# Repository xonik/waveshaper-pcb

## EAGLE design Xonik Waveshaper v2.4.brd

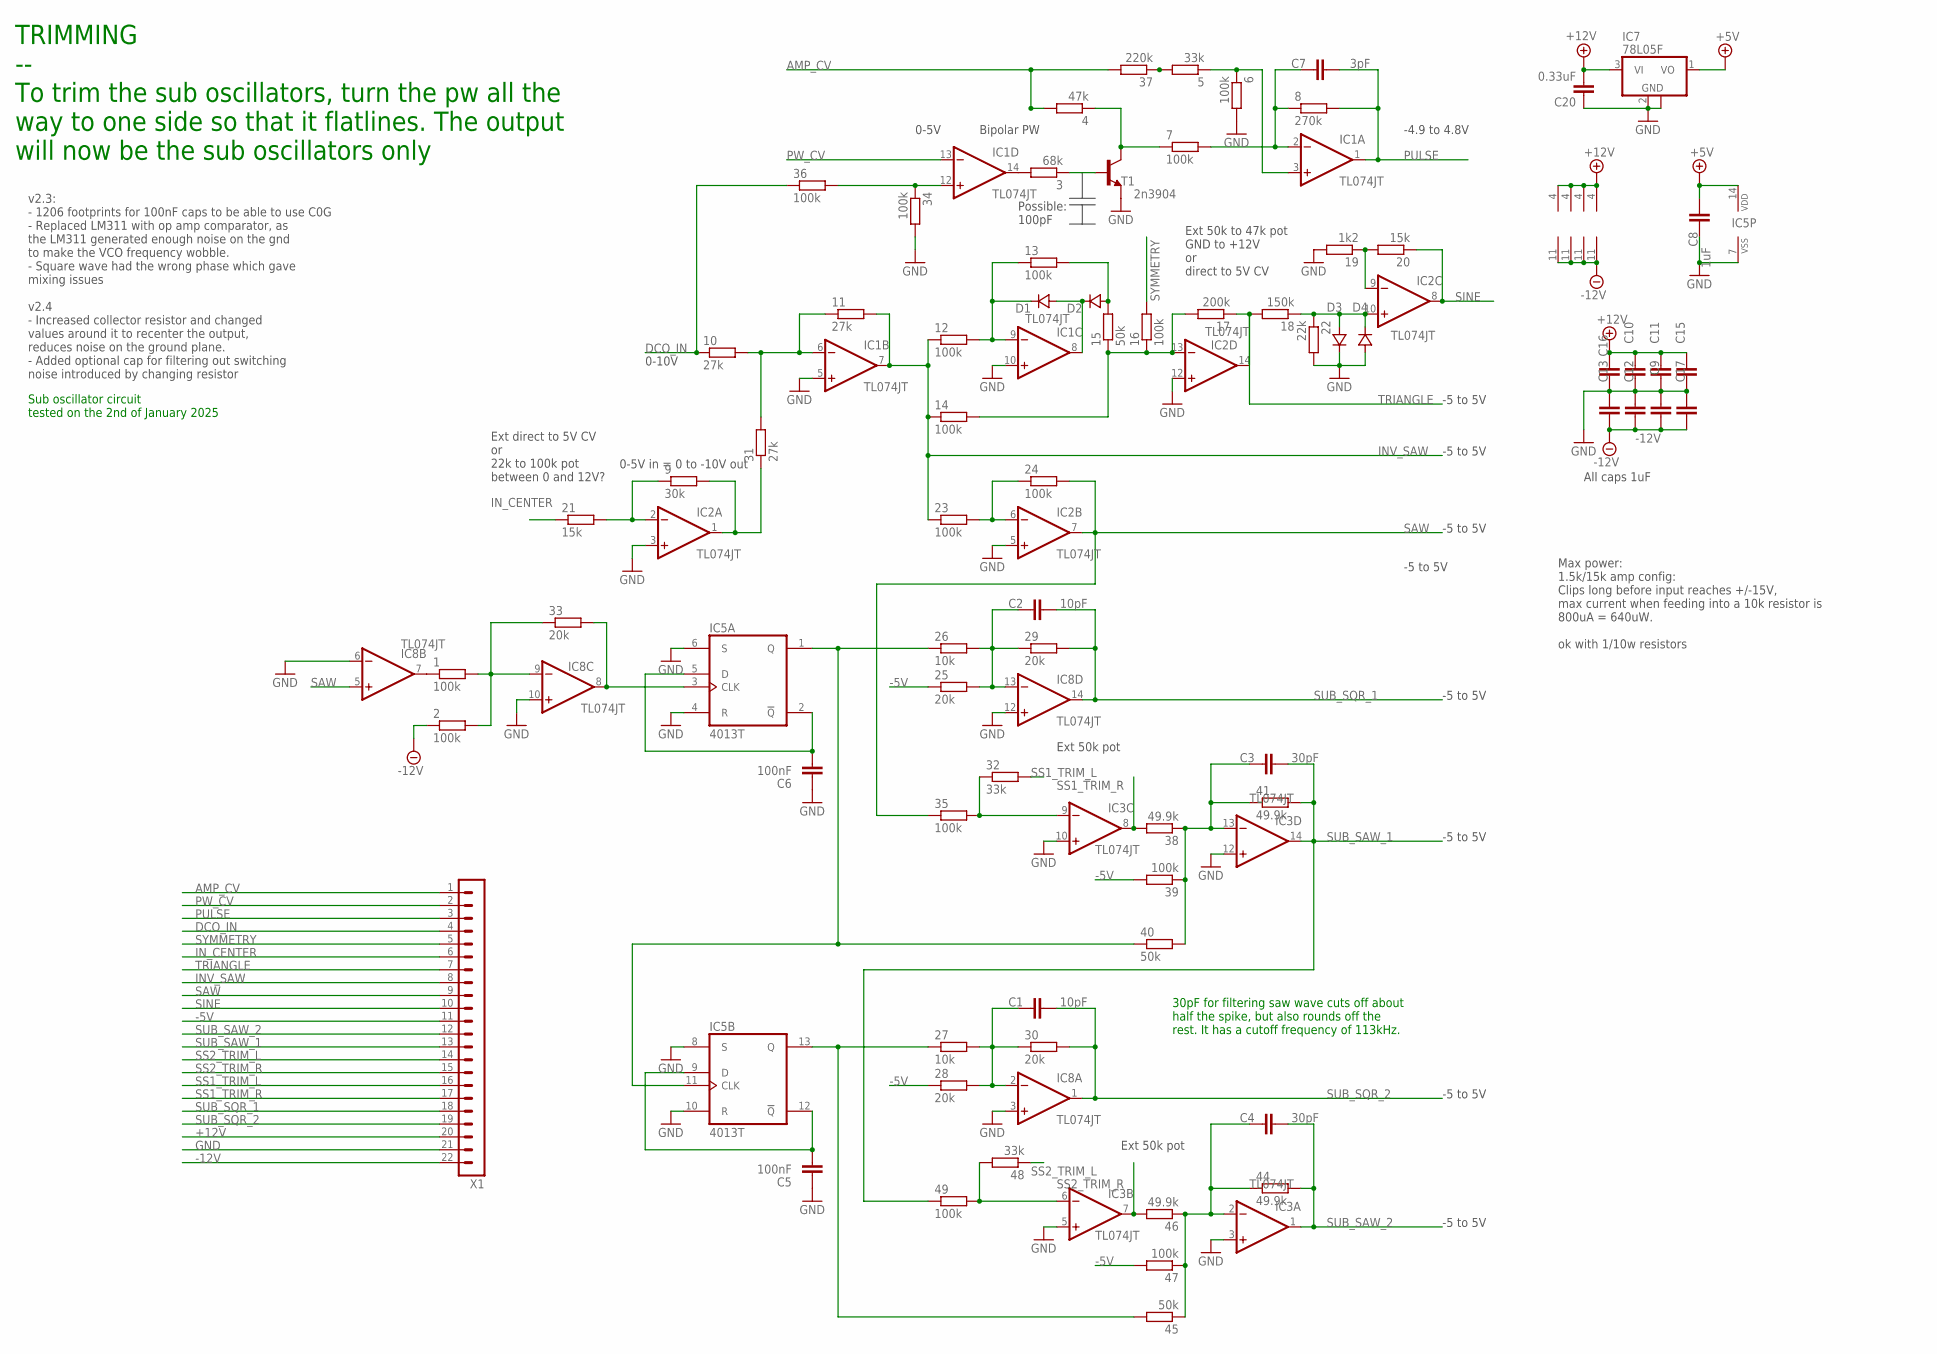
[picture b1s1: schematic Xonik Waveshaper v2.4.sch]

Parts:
1, 2, 6, 7, 12, 14, 16, 23, 35, 39, 47, 49: 100k; R0603
3: 68k; R0603
4: 47k; R0603
5, 32, 48: 33k; R0603
8: 270k; R0603
9: 30k; R0603
10, 11, 31: 27k; R0603
13, 24, 34, 36: 100k; R0402
15, 40, 45: 50k; R0603
17: 200k; R0603
18: 150k; R0603
19: 1k2; R0603
20, 21: 15k; R0603
22: 22k; R0603
25, 28, 29, 30, 33: 20k; R0603
26, 27: 10k; R0603
37: 220k; R0603
38, 41, 44, 46: 49.9k; R0603
C1, C2: 10pF; C0603-J
C3, C4: 30pF; C0603-J
C5, C6: 100nF; C1206
C7: 3pF; C0603-J
C8, C9, C10, C11, C12, C13, C15, C16, C17: 1uF; C0402-J
C20: 0.33uF; C0603-J
D1, D2, D3, D4: 1N41480805; D0805-J
IC1, IC2, IC3, IC8: TL074JT; TSSOP14J
IC5: 4013T; TSSOP14J
IC7: 78L05F; SOT89
T1: 2n3904; SOT23-BEC
X1: MA22-1JN; MA22N-1J

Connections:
+5V: C8.2, IC5.14 (VDD), IC7.1 (VO)
+12V: C10.2, C11.2, C15.2, C16.2, C20.2, IC1.4 (V+), IC2.4 (V+), IC3.4 (V+), IC7.3 (VI), IC8.4 (V+), X1.20
-5V: 25.1, 28.1, 39.2, 47.2, X1.11
-12V: 2.1, C9.1, C12.1, C13.1, C17.1, IC1.11 (V-), IC2.11 (V-), IC3.11 (V-), IC8.11 (V-), X1.22
AMP_CV: 4.2, 37.2, X1.1
DCO_IN: 10.1, 36.1, X1.4
GND: 6.2, 19.2, 22.2, 34.2, C5.1, C6.1, C8.1, C9.2, C10.1, C11.1, C12.2, C13.2, C15.1, C16.1, C17.2, C20.1, D3.C, D4.A, IC1.5 (+IN), IC1.10 (+IN), IC2.3 (+IN), IC2.5 (+IN), IC2.12 (+IN), IC3.3 (+IN), IC3.5 (+IN), IC3.10 (+IN), IC3.12 (+IN), IC5.4 (R), IC5.6 (S), IC5.7 (VSS), IC5.8 (S), IC5.10 (R), IC7.2 (GND), IC7.2@1 (GND), IC8.3 (+IN), IC8.6 (-IN), IC8.10 (+IN), IC8.12 (+IN), T1.E, X1.21
INV_SAW: 11.2, 12.1, 14.1, 23.1, IC1.7 (OUT), X1.8
IN_CENTER: 21.1, X1.6
unnamed: 9.1, 21.2, IC2.2 (-IN)
unnamed: 3.2, IC1.14 (OUT)
unnamed: 3.1, T1.B
unnamed: 4.1, 7.1, T1.C
unnamed: 5.1, 6.1, IC1.3 (+IN)
unnamed: 7.2, 8.1, C7.1, IC1.2 (-IN)
unnamed: 1.1, IC8.7 (OUT)
unnamed: 34.1, 36.2, IC1.12 (+IN)
unnamed: 1.2, 2.2, 33.1, IC8.9 (-IN)
unnamed: 10.2, 11.1, 31.2, IC1.6 (-IN)
unnamed: 12.2, 13.1, D1.C, IC1.9 (-IN)
unnamed: D1.A, D2.C, IC1.8 (OUT)
unnamed: 13.2, 15.2, D2.A
unnamed: 14.2, 15.1, 16.1, 17.2, IC2.13 (-IN)
unnamed: 23.2, 24.1, IC2.6 (-IN)
unnamed: 5.2, 37.1
unnamed: 33.2, IC5.3 (CLK), IC8.8 (OUT)
unnamed: 25.2, 26.2, 29.1, C2.1, IC8.13 (-IN)
unnamed: 48.2, 49.2, IC3.6 (-IN)
unnamed: 27.2, 28.2, 30.1, C1.1, IC8.2 (-IN)
unnamed: 32.1, 35.2, IC3.9 (-IN)
unnamed: 38.1, 39.1, 40.2, 41.1, C3.1, IC3.13 (-IN)
unnamed: 44.1, 45.1, 46.1, 47.1, C4.1, IC3.2 (-IN)
unnamed: C6.2, IC5.2 (!Q), IC5.5 (D)
unnamed: 26.1, 40.1, IC5.1 (Q), IC5.11 (CLK)
unnamed: C5.2, IC5.9 (D), IC5.12 (!Q)
unnamed: 27.1, 45.2, IC5.13 (Q)
unnamed: 19.1, 20.2, IC2.9 (-IN)
unnamed: 18.1, 22.1, D3.A, D4.C, IC2.10 (+IN)
unnamed: 9.2, 31.1, IC2.1 (OUT)
PULSE: 8.2, C7.2, IC1.1 (OUT), X1.3
PW_CV: IC1.13 (-IN), X1.2
SAW: 24.2, 35.1, IC2.7 (OUT), IC8.5 (+IN), X1.9
SINE: 20.1, IC2.8 (OUT), X1.10
SS1_TRIM_L: 32.2, X1.16
SS1_TRIM_R: 38.2, IC3.8 (OUT), X1.17
SS2_TRIM_L: 48.1, X1.14
SS2_TRIM_R: 46.2, IC3.7 (OUT), X1.15
SUB_SAW_1: 41.2, 49.1, C3.2, IC3.14 (OUT), X1.13
SUB_SAW_2: 44.2, C4.2, IC3.1 (OUT), X1.12
SUB_SQR_1: 29.2, C2.2, IC8.14 (OUT), X1.18
SUB_SQR_2: 30.2, C1.2, IC8.1 (OUT), X1.19
SYMMETRY: 16.2, X1.5
TRIANGLE: 17.1, 18.2, IC2.14 (OUT), X1.7

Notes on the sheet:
All caps 1uF
Ext direct to 5V CV or 22k to 100k pot between 0 and 12V?
Ext 50k to 47k pot GND to +12V or direct to 5V CV
Ext 50k pot
30pF for filtering saw wave cuts off about half the spike, but also rounds off the rest. It has a cutoff frequency of 113kHz.
Max power: 1.5k/15k amp config: Clips long before input reaches +/-15V, max current when feeding into a 10k resistor is 800uA = 640uW. ok with 1/10w resistors
0-5V in = 0 to -10V out
0-10V
0-5V
-4.9 to 4.8V
Bipolar PW
-5 to 5V
TRIMMING -- To trim the sub oscillators, turn the pw all the way to one side so that it flatlines. The output will now be the sub oscillators only
v2.3: - 1206 footprints for 100nF caps to be able to use C0G - Replaced LM311 with op amp comparator, as the LM311 generated enough noise on the gnd to make the VCO frequency wobble. - Square wave had the wrong phase which gave mixing issues v2.4 - Increased collector resistor and changed values ar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
Sub oscillator circuit tested on the 2nd of January 2025
Possible: 100pF

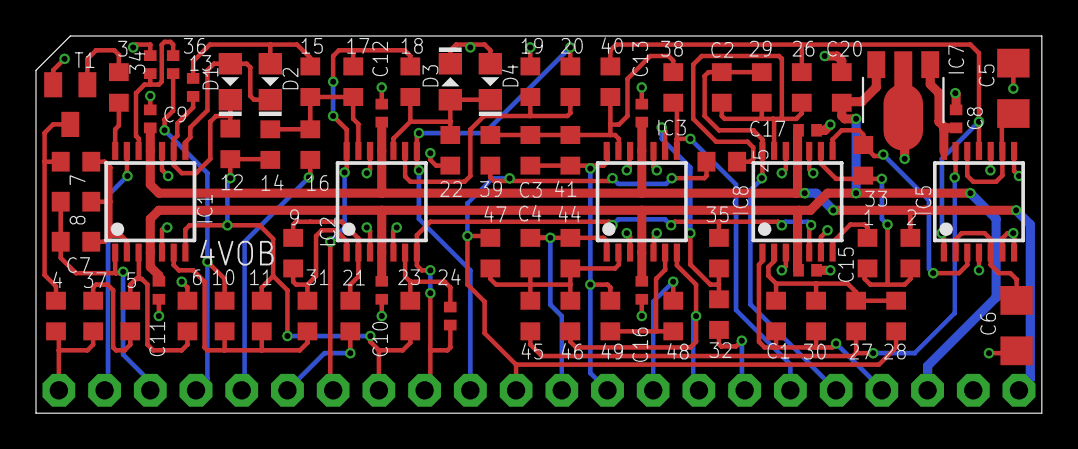
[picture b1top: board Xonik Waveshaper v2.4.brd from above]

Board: 4 copper layers, 55.9 x 21.0 mm, 77 parts (1 on the bottom side), 53 nets.

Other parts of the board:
U$1: XONIK_LOGO_40

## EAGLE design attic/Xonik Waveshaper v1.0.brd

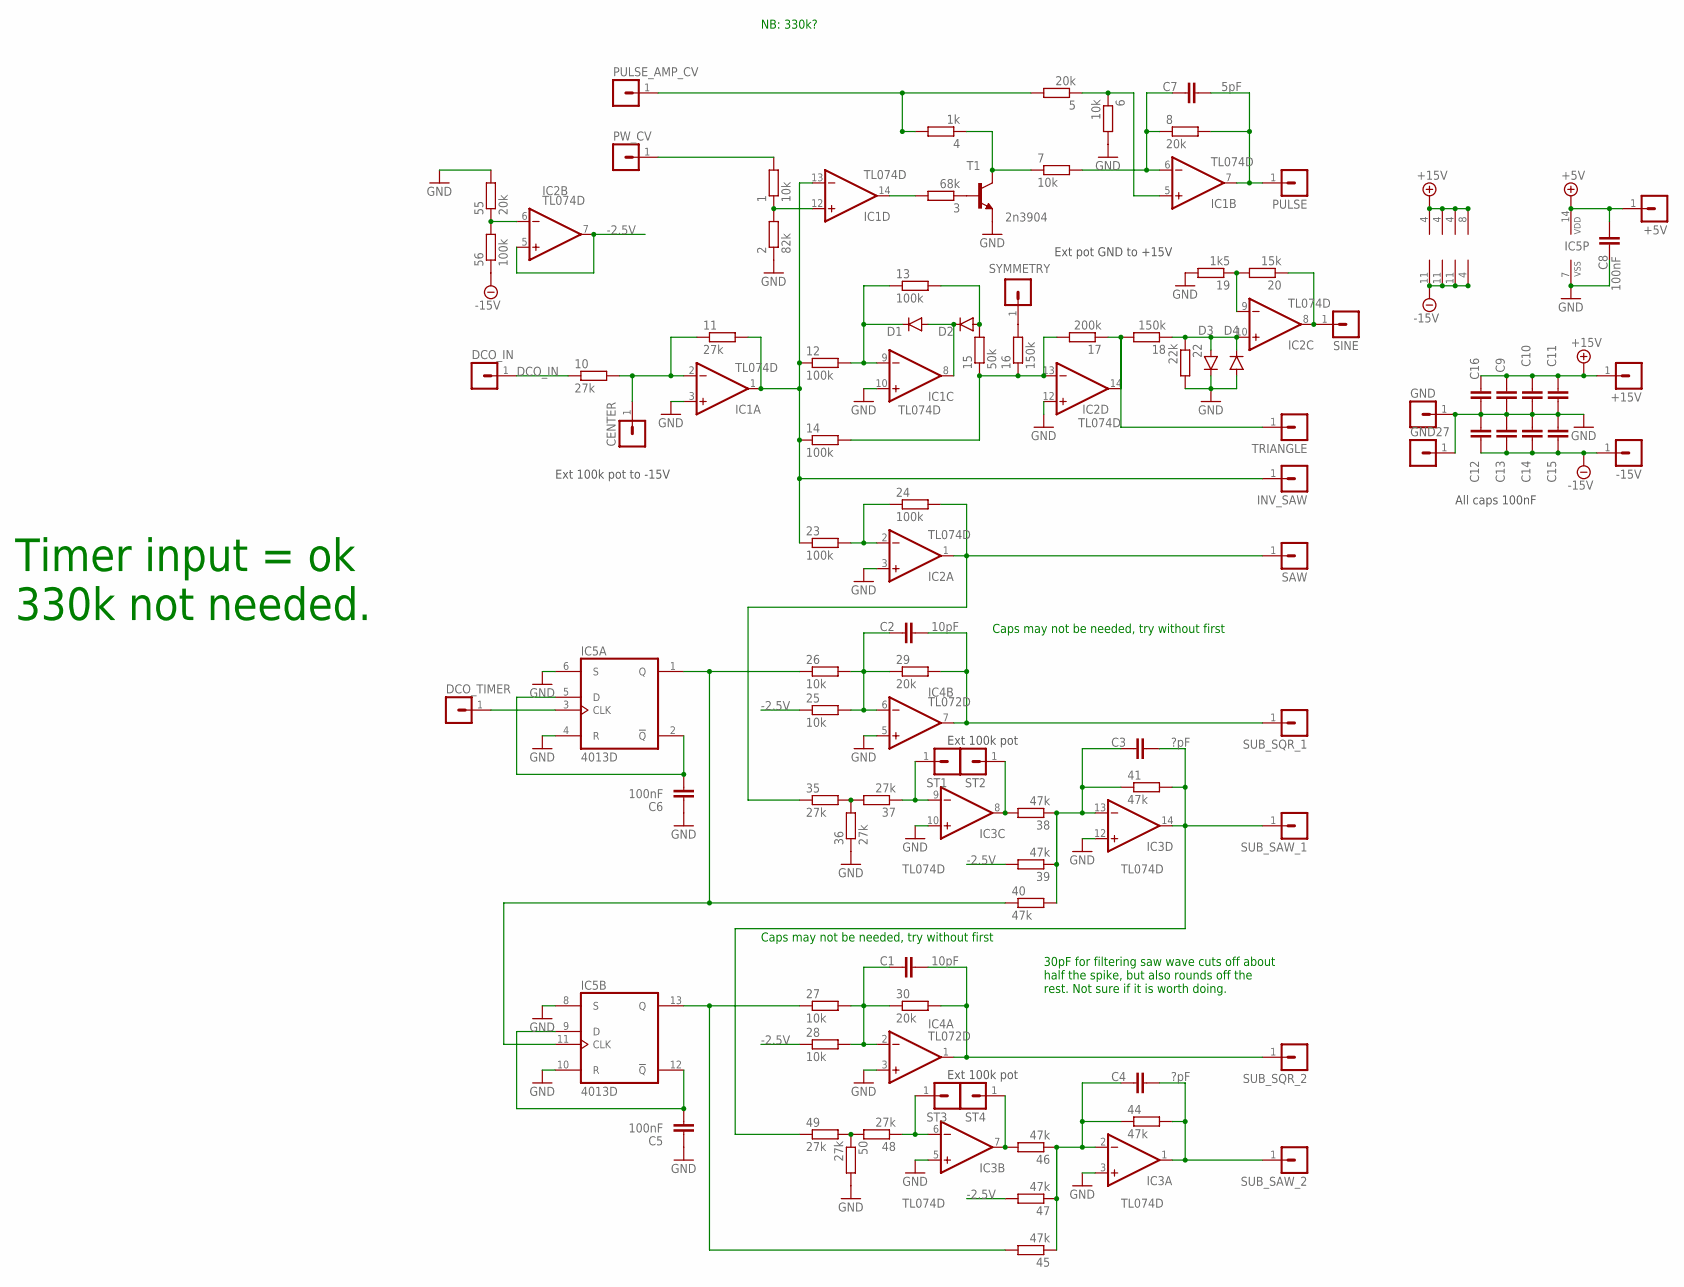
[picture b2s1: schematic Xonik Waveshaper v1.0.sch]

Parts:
1, 6, 7, 25, 26, 27, 28: 10k; R0805
2: 82k; R0805
3: 68k; R0805
4: 1k; R0805
5, 8, 29, 30, 55: 20k; R0805
10, 11, 35, 36, 37, 48, 49, 50: 27k; R0805
12, 13, 14, 23, 24, 56: 100k; R0805
15: 50k; R0805
16, 18: 150k; R0805
17: 200k; R0805
19: 1k5; R0805
20: 15k; R0805
22: 22k; R0805
38, 39, 40, 41, 44, 45, 46, 47: 47k; R0805
+5V, +15V: MA01-1JP; SIP-PIN01-1J
-15V: MA01-1JP; SIP-PIN01-1J
C1, C2: 10pF; C0805
C3, C4: ?pF; C0805
C5, C6, C8: 100nF; C0805
C7: 5pF; C0805
C9, C10, C11, C12, C13, C14, C15, C16: 100nF; C0603K
CENTER: MA01-1JP; SIP-PIN01-1J
D1, D2, D3, D4: 1N41480805; D0805-J
DCO_IN: MA01-1JP; SIP-PIN01-1J
DCO_TIMER: MA01-1JP; SIP-PIN01-1J
GND, GND27: MA01-1JP; SIP-PIN01-1J
IC1, IC2, IC3: TL074D; SO14
IC4: TL072D; SO08J
IC5: 4013D; SO14J
INV_SAW: MA01-1JP; SIP-PIN01-1J
PULSE: MA01-1JP; SIP-PIN01-1J
PULSE_AMP_CV: MA01-1JP; SIP-PIN01-1J
PW_CV: MA01-1JP; SIP-PIN01-1J
SAW: MA01-1JP; SIP-PIN01-1J
SINE: MA01-1JP; SIP-PIN01-1J
ST1, ST2, ST3, ST4: MA01-1JP; SIP-PIN01-1J
SUB_SAW_1, SUB_SAW_2: MA01-1JP; SIP-PIN01-1J
SUB_SQR_1, SUB_SQR_2: MA01-1JP; SIP-PIN01-1J
SYMMETRY: MA01-1JP; SIP-PIN01-1J
T1: 2n3904; SOT23-BEC
TRIANGLE: MA01-1JP; SIP-PIN01-1J

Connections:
+5V: +5V.1, C8.2, IC5.14 (VDD)
+15V: +15V.1, C9.2, C10.2, C11.2, C16.2, IC1.4 (V+), IC2.4 (V+), IC3.4 (V+), IC4.8 (V+)
-2.5V: 25.1, 28.1, 39.2, 47.2, IC2.5 (+IN), IC2.7 (OUT)
-15V: 56.1, -15V.1, C12.1, C13.1, C14.1, C15.1, IC1.11 (V-), IC2.11 (V-), IC3.11 (V-), IC4.4 (V-)
AMP_CV: 4.2, 5.2, PULSE_AMP_CV.1
DCO_IN: 10.1, DCO_IN.1
GND: 2.1, 6.2, 19.2, 22.2, 36.1, 50.2, 55.2, C5.1, C6.1, C8.1, C9.1, C10.1, C11.1, C12.2, C13.2, C14.2, C15.2, C16.1, D3.C, D4.A, GND.1, GND27.1, IC1.3 (+IN), IC1.10 (+IN), IC2.3 (+IN), IC2.12 (+IN), IC3.3 (+IN), IC3.5 (+IN), IC3.10 (+IN), IC3.12 (+IN), IC4.3 (+IN), IC4.5 (+IN), IC5.4 (R), IC5.6 (S), IC5.7 (VSS), IC5.8 (S), IC5.10 (R), T1.E
unnamed: 1.1, 2.2, IC1.12 (+IN)
unnamed: 3.2, IC1.14 (OUT)
unnamed: 3.1, T1.B
unnamed: 4.1, 7.1, T1.C
unnamed: 5.1, 6.1, IC1.5 (+IN)
unnamed: 7.2, 8.1, C7.1, IC1.6 (-IN)
unnamed: 8.2, C7.2, IC1.7 (OUT), PULSE.1
unnamed: 11.2, 12.1, 14.1, 23.1, IC1.1 (OUT), IC1.13 (-IN), INV_SAW.1
unnamed: 10.2, 11.1, CENTER.1, IC1.2 (-IN)
unnamed: 12.2, 13.1, D1.C, IC1.9 (-IN)
unnamed: D1.A, D2.C, IC1.8 (OUT)
unnamed: 13.2, 15.2, D2.A
unnamed: 14.2, 15.1, 16.1, 17.2, IC2.13 (-IN)
unnamed: 23.2, 24.1, IC2.2 (-IN)
unnamed: 24.2, 35.1, IC2.1 (OUT), SAW.1
unnamed: 29.2, C2.2, IC4.7 (OUT), SUB_SQR_1.1
unnamed: 30.2, C1.2, IC4.1 (OUT), SUB_SQR_2.1
unnamed: 25.2, 26.2, 29.1, C2.1, IC4.6 (-IN)
unnamed: 46.2, IC3.7 (OUT), ST4.1
unnamed: 48.2, 49.2, 50.1
unnamed: 27.2, 28.2, 30.1, C1.1, IC4.2 (-IN)
unnamed: 35.2, 36.2, 37.2
unnamed: 37.1, IC3.9 (-IN), ST1.1
unnamed: 38.1, 39.1, 40.2, 41.1, C3.1, IC3.13 (-IN)
unnamed: 41.2, 49.1, C3.2, IC3.14 (OUT), SUB_SAW_1.1
unnamed: 48.1, IC3.6 (-IN), ST3.1
unnamed: 44.1, 45.1, 46.1, 47.1, C4.1, IC3.2 (-IN)
unnamed: 44.2, C4.2, IC3.1 (OUT), SUB_SAW_2.1
unnamed: C6.2, IC5.2 (!Q), IC5.5 (D)
unnamed: 26.1, 40.1, IC5.1 (Q), IC5.11 (CLK)
unnamed: 55.1, 56.2, IC2.6 (-IN)
unnamed: C5.2, IC5.9 (D), IC5.12 (!Q)
unnamed: 27.1, 45.2, IC5.13 (Q)
unnamed: 19.1, 20.2, IC2.9 (-IN)
unnamed: 16.2, SYMMETRY.1
unnamed: 17.1, 18.2, IC2.14 (OUT), TRIANGLE.1
unnamed: 18.1, 22.1, D3.A, D4.C, IC2.10 (+IN)
unnamed: 20.1, IC2.8 (OUT), SINE.1
unnamed: 38.2, IC3.8 (OUT), ST2.1
PW_CV: 1.2, PW_CV.1
SQR: DCO_TIMER.1, IC5.3 (CLK)

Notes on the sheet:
NB: 330k?
All caps 100nF
Ext 100k pot to -15V
Ext pot GND to +15V
Ext 100k pot
Timer input = ok 330k not needed.
30pF for filtering saw wave cuts off about half the spike, but also rounds off the rest. Not sure if it is worth doing.
Caps may not be needed, try without first

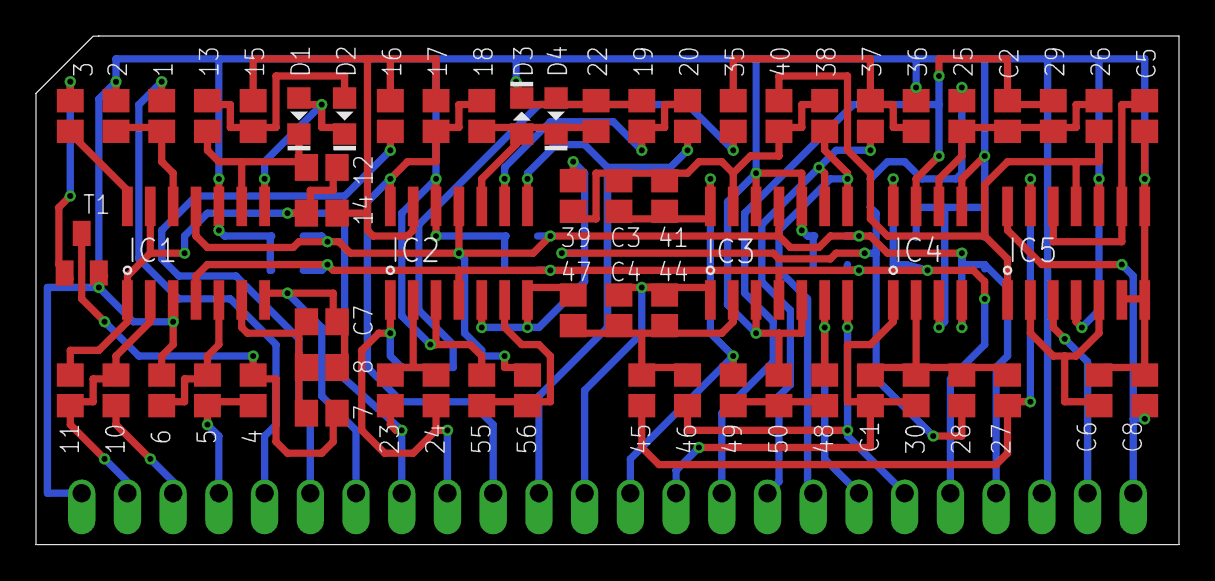
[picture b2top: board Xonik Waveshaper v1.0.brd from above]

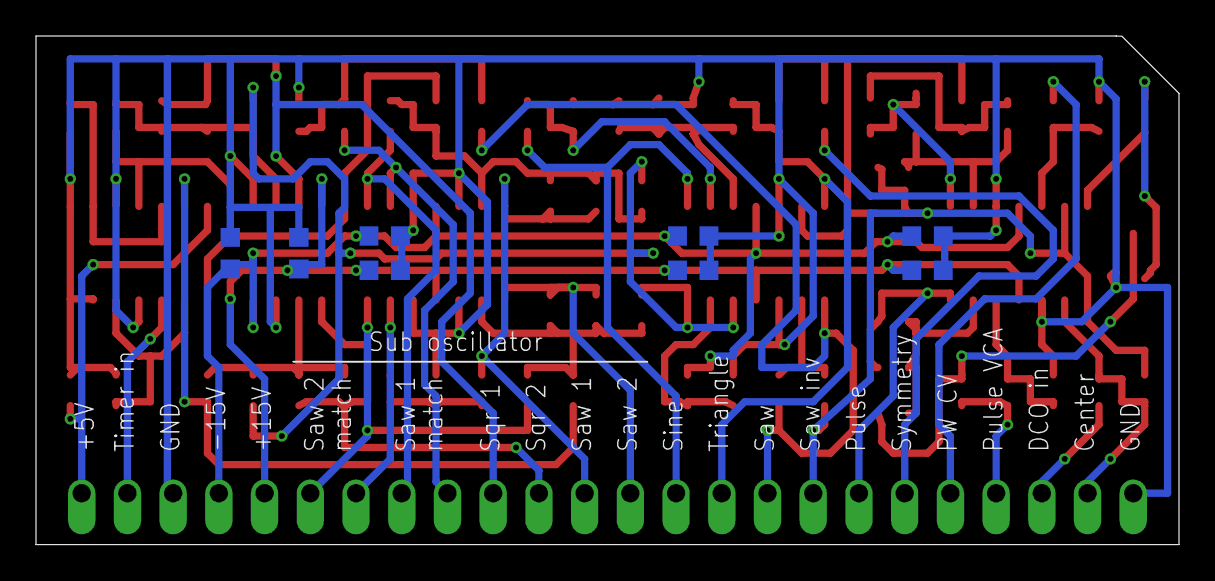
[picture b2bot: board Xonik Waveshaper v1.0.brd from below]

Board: 2 copper layers, 63.5 x 28.3 mm, 94 parts (8 on the bottom side), 48 nets.

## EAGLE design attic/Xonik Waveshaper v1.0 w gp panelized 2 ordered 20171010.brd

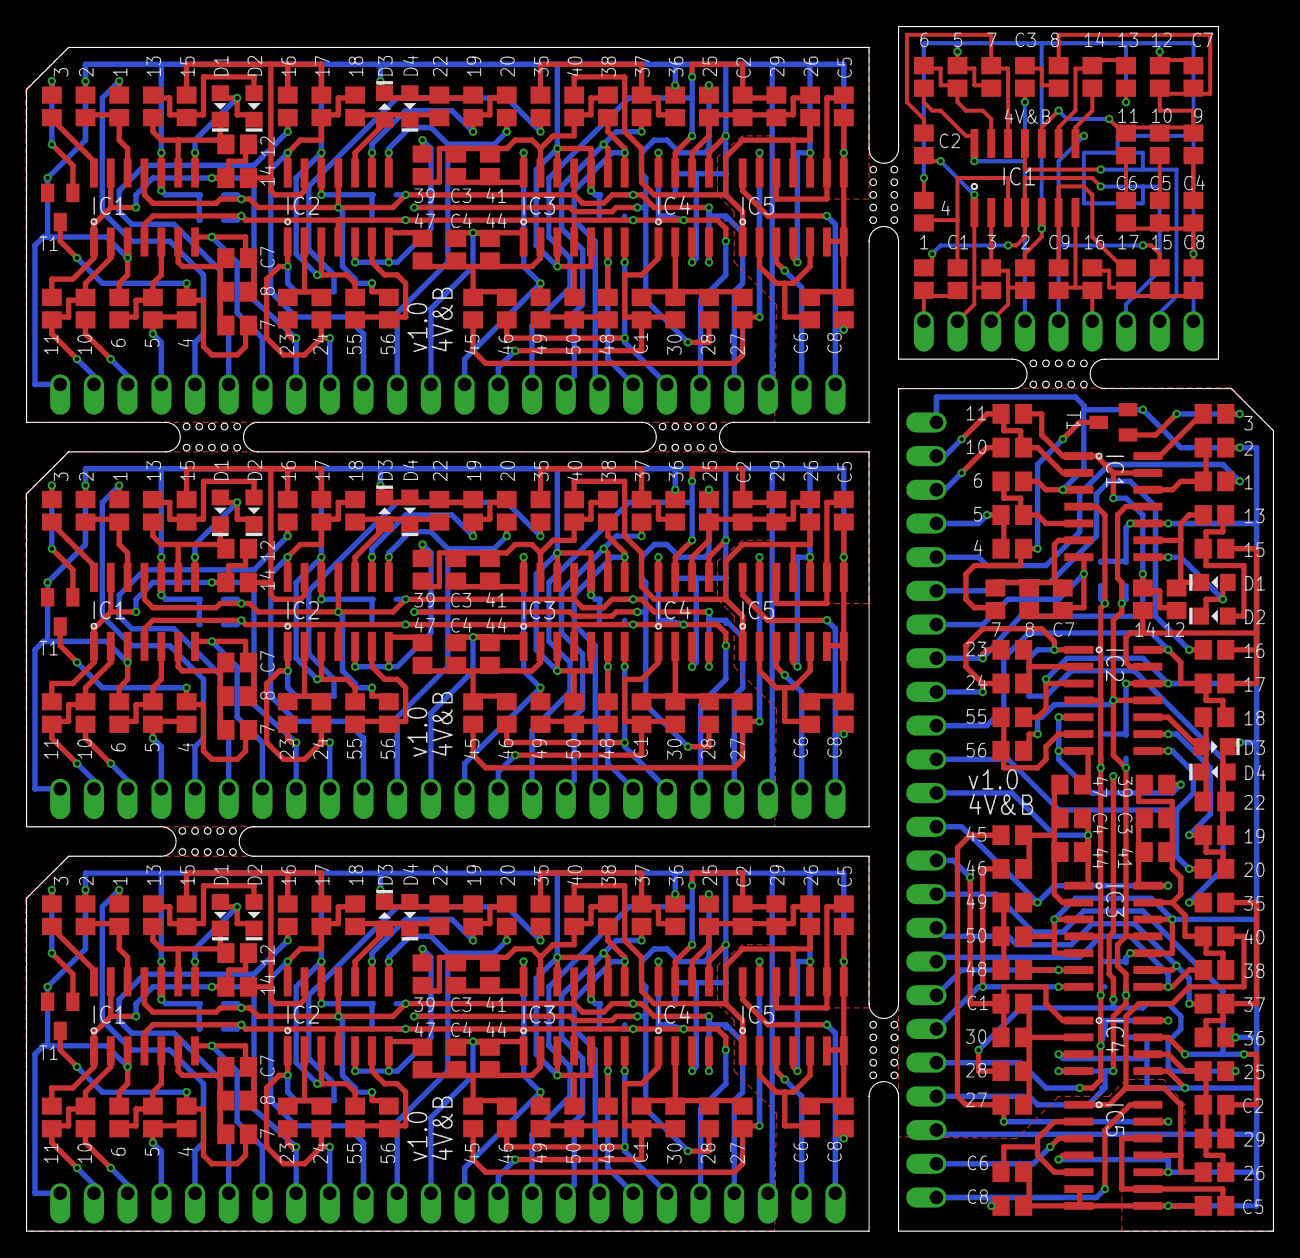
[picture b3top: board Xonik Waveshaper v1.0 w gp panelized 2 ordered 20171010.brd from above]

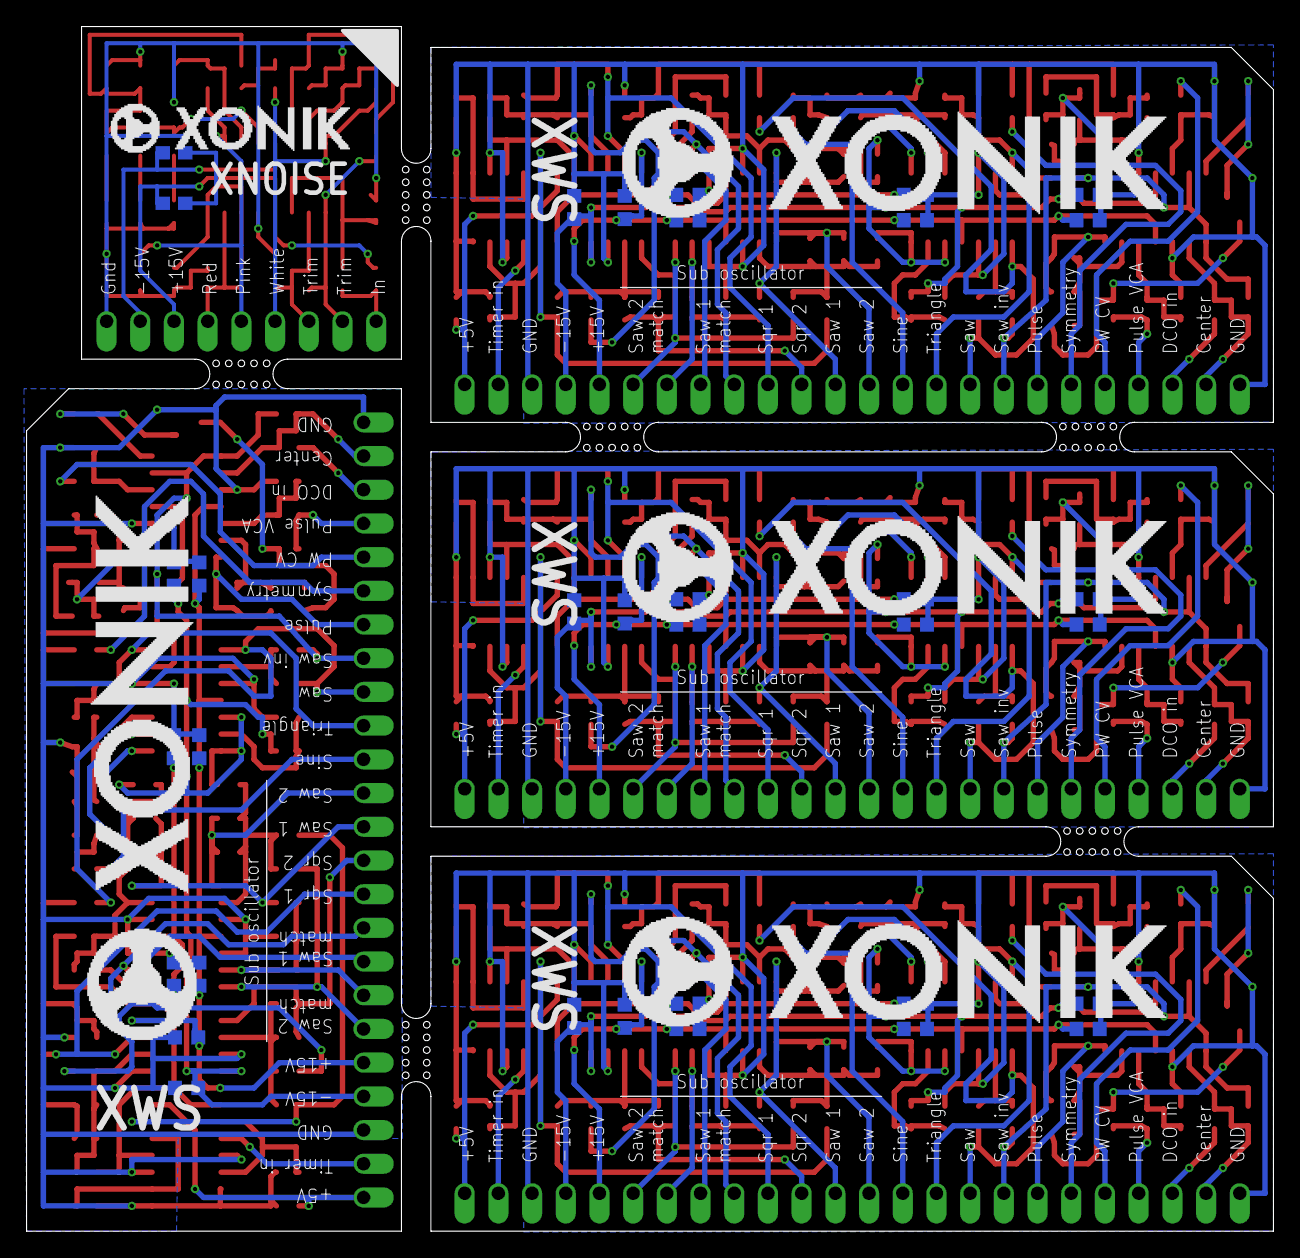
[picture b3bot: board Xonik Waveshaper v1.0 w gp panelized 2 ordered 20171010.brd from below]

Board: 2 copper layers, 94.0 x 90.8 mm, 414 parts (34 on the bottom side), 212 nets.

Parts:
1, 6, 7, 9, 25, 26, 27, 28, 34, 42, 67, 68, 69, 70, 89, 94, 95, 111, 112, 113, 114, 133, 138, 139, 155, 156, 157, 158, 186: 10k; R0805
2, 21, 90, 134: 82k; R0805
3, 31, 91, 135, 184: 68k; R0805
4, 32, 92, 136, 178, 181, 189: 1k; R0805
5, 8, 29, 30, 33, 43, 55, 71, 72, 87, 93, 96, 115, 116, 131, 137, 140, 159, 160, 175, 179, 182, 190: 20k; R0805
10, 11, 35, 36, 37, 48, 49, 50, 51, 52, 73, 74, 75, 84, 85, 86, 97, 98, 117, 118, 119, 128, 129, 130, 141, 142, 161, 162, 163, 172, 173, 174: 27k; R0805
12, 13, 14, 23, 24, 53, 54, 56, 57, 65, 66, 88, 99, 100, 101, 109, 110, 132, 143, 144, 145, 153, 154, 176, 180, 183: 100k; R0805
15, 58, 102, 146: 50k; R0805
16, 18, 59, 61, 103, 105, 147, 149: 150k; R0805
17, 60, 104, 148: 200k; R0805
19, 62, 106, 150: 1k5; R0805
20, 63, 107, 151, 192: 15k; R0805
22, 64, 108, 152: 22k; R0805
38, 39, 40, 41, 44, 45, 46, 47, 76, 77, 78, 79, 80, 81, 82, 83, 120, 121, 122, 123, 124, 125, 126, 127, 164, 165, 166, 167, 168, 169, 170, 171: 47k; R0805
177: 220k; R0805
185: 33.2k; R0805
187: 3k; R0805
188: 1M; R0805
191: 4k7; R0805
193: 301k; R0805
+5V, +5V1, +5V2, +5V3, +15V, +15V1, +15V2, +15V3, +15V4: SIP-PIN01-1J
-15V, -15V1, -15V2, -15V3, -15V4: SIP-PIN01-1J
C1, C2, C17, C18, C33, C34, C49, C50: 10pF; C0805
C3, C4, C19, C20, C35, C36, C51, C52: ?pF; C0805
C5, C6, C8, C21, C22, C32, C37, C38, C48, C53, C54, C64: 100nF; C0805
C7, C23, C39, C55: 5pF; C0805
C9, C10, C11, C12, C13, C14, C15, C16, C24, C25, C26, C27, C28, C29, C30, C31, C40, C41, C42, C43, C44, C45, C46, C47, C56, C57, C58, C59, C60, C61, C62, C63: 100nF; C0603K
C65, C66, C67: 470n; C0805
C68: 100n; C0805
C69: 22n; C0805
C70: 10n; C0805
C71: 3n3; C0805
C72: 220n; C0805
C73: 2n2; C0805
C74, C75: C0603
CENTER, CENTER1, CENTER2, CENTER3: SIP-PIN01-1J
D1, D2, D3, D4, D5, D6, D7, D8, D9, D10, D11, D12, D13, D14, D15, D16: 1N41480805; D0805-J
DCO_IN, DCO_IN1, DCO_IN2, DCO_IN3: SIP-PIN01-1J
DCO_TIMER, DCO_TIMER1, DCO_TIMER2, DCO_TIMER3: SIP-PIN01-1J
GND, GND1, GND2, GND3, GND4, GND5, GND6, GND7, GND27: SIP-PIN01-1J
IC1, IC2, IC3, IC6, IC7, IC8, IC11, IC12, IC13, IC16, IC17, IC18, IC21: TL074D; SO14
IC4, IC10, IC15, IC20: TL072D; SO08J
IC5, IC9, IC14, IC19: 4013D; SO14J
INV_SAW, INV_SAW1, INV_SAW2, INV_SAW3: SIP-PIN01-1J
LEVEL1, LEVEL2: SIP-PIN01-1J
NOISE_IN: SIP-PIN01-1J
PINK_OUT: SIP-PIN01-1J
PULSE, PULSE1, PULSE2, PULSE3: SIP-PIN01-1J
PULSE_AMP_CV, PULSE_AMP_CV1, PULSE_AMP_CV2, PULSE_AMP_CV3: SIP-PIN01-1J
PW_CV, PW_CV1, PW_CV2, PW_CV3: SIP-PIN01-1J
RED_OUT: SIP-PIN01-1J
SAW, SAW1, SAW2, SAW3: SIP-PIN01-1J
SINE, SINE1, SINE2, SINE3: SIP-PIN01-1J
ST1, ST2, ST3, ST4, ST5, ST6, ST7, ST8, ST9, ST10, ST11, ST12, ST13, ST14, ST15, ST16: SIP-PIN01-1J
SUB_SAW_1, SUB_SAW_2, SUB_SAW_3, SUB_SAW_4, SUB_SAW_5, SUB_SAW_6, SUB_SAW_7, SUB_SAW_8: SIP-PIN01-1J
SUB_SQR_1, SUB_SQR_2, SUB_SQR_3, SUB_SQR_4, SUB_SQR_5, SUB_SQR_6, SUB_SQR_7, SUB_SQR_8: SIP-PIN01-1J
SYMMETRY, SYMMETRY1, SYMMETRY2, SYMMETRY3: SIP-PIN01-1J
T1, T2, T3, T4: 2n3904; SOT23-BEC
TRIANGLE, TRIANGLE1, TRIANGLE2, TRIANGLE3: SIP-PIN01-1J
WHITE_OUT: SIP-PIN01-1J

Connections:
+5V: +5V.1, C8.2, IC5.14
+5V1: +5V1.1, C32.2, IC9.14
+5V2: +5V2.1, C48.2, IC14.14
+5V3: +5V3.1, C64.2, IC19.14
+15V: +15V.1, C9.2, C10.2, C11.2, C16.2, IC1.4, IC2.4, IC3.4, IC4.8
+15V1: +15V1.1, C24.2, C25.2, C26.2, C27.2, IC6.4, IC7.4, IC8.4, IC10.8
+15V2: +15V2.1, C40.2, C41.2, C42.2, C43.2, IC11.4, IC12.4, IC13.4, IC15.8
+15V3: +15V3.1, C56.2, C57.2, C58.2, C59.2, IC16.4, IC17.4, IC18.4, IC20.8
+15V4: 177.2, +15V4.1, C74.2, IC21.4
-2.5V: 25.1, 28.1, 39.2, 47.2, IC2.5, IC2.7
-2.5V1: 67.1, 70.1, 77.2, 83.2, IC7.5, IC7.7
-2.5V2: 111.1, 114.1, 121.2, 127.2, IC12.5, IC12.7
-2.5V3: 155.1, 158.1, 165.2, 171.2, IC17.5, IC17.7
-15V: 56.1, -15V.1, C12.1, C13.1, C14.1, C15.1, IC1.11, IC2.11, IC3.11, IC4.4
-15V1: 88.1, -15V1.1, C28.1, C29.1, C30.1, C31.1, IC6.11, IC7.11, IC8.11, IC10.4
-15V2: 132.1, -15V2.1, C44.1, C45.1, C46.1, C47.1, IC11.11, IC12.11, IC13.11, IC15.4
-15V3: 176.1, -15V3.1, C60.1, C61.1, C62.1, C63.1, IC16.11, IC17.11, IC18.11, IC20.4
-15V4: -15V4.1, C75.1, IC21.11
AMP_CV: 4.2, 5.2, PULSE_AMP_CV.1
AMP_CV1: 32.2, 33.2, PULSE_AMP_CV1.1
AMP_CV2: 92.2, 93.2, PULSE_AMP_CV2.1
AMP_CV3: 136.2, 137.2, PULSE_AMP_CV3.1
DCO_IN: 10.1, DCO_IN.1
DCO_IN1: 51.1, DCO_IN1.1
DCO_IN2: 97.1, DCO_IN2.1
DCO_IN3: 141.1, DCO_IN3.1
GND: 2.1, 6.2, 19.2, 22.2, 36.1, 50.2, 55.2, C5.1, C6.1, C8.1, C9.1, C10.1, C11.1, C12.2, C13.2, C14.2, C15.2, C16.1, D3.C, D4.A, GND.1, GND27.1, IC1.3, IC1.10, IC2.3, IC2.12, IC3.3, IC3.5, IC3.10, IC3.12, IC4.3, IC4.5, IC5.4, IC5.6, IC5.7, IC5.8, IC5.10, T1.E
GND1: 21.1, 34.2, 62.2, 64.2, 74.1, 86.2, 87.2, C21.1, C22.1, C24.1, C25.1, C26.1, C27.1, C28.2, C29.2, C30.2, C31.2, C32.1, D7.C, D8.A, GND1.1, GND2.1, IC6.3, IC6.10, IC7.3, IC7.12, IC8.3, IC8.5, IC8.10, IC8.12, IC9.4, IC9.6, IC9.7, IC9.8, IC9.10, IC10.3, IC10.5, T2.E
GND2: 90.1, 94.2, 106.2, 108.2, 118.1, 130.2, 131.2, C37.1, C38.1, C40.1, C41.1, C42.1, C43.1, C44.2, C45.2, C46.2, C47.2, C48.1, D11.C, D12.A, GND3.1, GND4.1, IC11.3, IC11.10, IC12.3, IC12.12, IC13.3, IC13.5, IC13.10, IC13.12, IC14.4, IC14.6, IC14.7, IC14.8, IC14.10, IC15.3, IC15.5, T3.E
GND3: 134.1, 138.2, 150.2, 152.2, 162.1, 174.2, 175.2, C53.1, C54.1, C56.1, C57.1, C58.1, C59.1, C60.2, C61.2, C62.2, C63.2, C64.1, D15.C, D16.A, GND5.1, GND6.1, IC16.3, IC16.10, IC17.3, IC17.12, IC18.3, IC18.5, IC18.10, IC18.12, IC19.4, IC19.6, IC19.7, IC19.8, IC19.10, IC20.3, IC20.5, T4.E
GND4: 178.2, 180.2, 181.1, 183.1, 188.2, 189.1, C68.1, C69.1, C70.1, C71.1, C72.1, C74.1, C75.2, GND7.1, IC21.5
unnamed: 1.1, 2.2, IC1.12
unnamed: 3.2, IC1.14
unnamed: 3.1, T1.B
unnamed: 4.1, 7.1, T1.C
unnamed: 5.1, 6.1, IC1.5
unnamed: 7.2, 8.1, C7.1, IC1.6
unnamed: 8.2, C7.2, IC1.7, PULSE.1
unnamed: 9.1, 21.2, IC6.12
unnamed: 11.2, 12.1, 14.1, 23.1, IC1.1, IC1.13, INV_SAW.1
unnamed: 10.2, 11.1, CENTER.1, IC1.2
unnamed: 12.2, 13.1, D1.C, IC1.9
unnamed: D1.A, D2.C, IC1.8
unnamed: 13.2, 15.2, D2.A
unnamed: 14.2, 15.1, 16.1, 17.2, IC2.13
unnamed: 23.2, 24.1, IC2.2
unnamed: 24.2, 35.1, IC2.1, SAW.1
unnamed: 29.2, C2.2, IC4.7, SUB_SQR_1.1
unnamed: 30.2, C1.2, IC4.1, SUB_SQR_2.1
unnamed: 25.2, 26.2, 29.1, C2.1, IC4.6
unnamed: 46.2, IC3.7, ST4.1
unnamed: 48.2, 49.2, 50.1
unnamed: 27.2, 28.2, 30.1, C1.1, IC4.2
unnamed: 35.2, 36.2, 37.2
unnamed: 37.1, IC3.9, ST1.1
unnamed: 31.2, IC6.14
unnamed: 38.1, 39.1, 40.2, 41.1, C3.1, IC3.13
unnamed: 41.2, 49.1, C3.2, IC3.14, SUB_SAW_1.1
unnamed: 48.1, IC3.6, ST3.1
unnamed: 44.1, 45.1, 46.1, 47.1, C4.1, IC3.2
unnamed: 44.2, C4.2, IC3.1, SUB_SAW_2.1
unnamed: C6.2, IC5.2, IC5.5
unnamed: 26.1, 40.1, IC5.1, IC5.11
unnamed: 55.1, 56.2, IC2.6
unnamed: C5.2, IC5.9, IC5.12
unnamed: 27.1, 45.2, IC5.13
unnamed: 19.1, 20.2, IC2.9
unnamed: 16.2, SYMMETRY.1
unnamed: 17.1, 18.2, IC2.14, TRIANGLE.1
unnamed: 18.1, 22.1, D3.A, D4.C, IC2.10
unnamed: 20.1, IC2.8, SINE.1
unnamed: 38.2, IC3.8, ST2.1
unnamed: 31.1, T2.B
unnamed: 32.1, 42.1, T2.C
unnamed: 33.1, 34.1, IC6.5
unnamed: 42.2, 43.1, C23.1, IC6.6
unnamed: 43.2, C23.2, IC6.7, PULSE1.1
unnamed: 52.2, 53.1, 57.1, 65.1, IC6.1, IC6.13, INV_SAW1.1
unnamed: 51.2, 52.1, CENTER1.1, IC6.2
unnamed: 53.2, 54.1, D5.C, IC6.9
unnamed: D5.A, D6.C, IC6.8
unnamed: 54.2, 58.2, D6.A
unnamed: 57.2, 58.1, 59.1, 60.2, IC7.13
unnamed: 65.2, 66.1, IC7.2
unnamed: 66.2, 73.1, IC7.1, SAW1.1
unnamed: 71.2, C18.2, IC10.7, SUB_SQR_3.1
unnamed: 72.2, C17.2, IC10.1, SUB_SQR_4.1
unnamed: 67.2, 68.2, 71.1, C18.1, IC10.6
unnamed: 69.2, 70.2, 72.1, C17.1, IC10.2
unnamed: 73.2, 74.2, 75.2
unnamed: 75.1, IC8.9, ST5.1
unnamed: 76.1, 77.1, 78.2, 79.1, C19.1, IC8.13
unnamed: 79.2, 85.1, C19.2, IC8.14, SUB_SAW_3.1
unnamed: 82.2, IC8.7, ST8.1
unnamed: 84.2, 85.2, 86.1
unnamed: 84.1, IC8.6, ST7.1
unnamed: 80.1, 81.1, 82.1, 83.1, C20.1, IC8.2
unnamed: 80.2, C20.2, IC8.1, SUB_SAW_4.1
unnamed: 87.1, 88.2, IC7.6
unnamed: C22.2, IC9.2, IC9.5
unnamed: 68.1, 78.1, IC9.1, IC9.11
unnamed: C21.2, IC9.9, IC9.12
unnamed: 69.1, 81.2, IC9.13
unnamed: 60.1, 61.2, IC7.14, TRIANGLE1.1
unnamed: 61.1, 64.1, D7.A, D8.C, IC7.10
unnamed: 62.1, 63.2, IC7.9
unnamed: 63.1, IC7.8, SINE1.1
unnamed: 59.2, SYMMETRY1.1
unnamed: 76.2, IC8.8, ST6.1
unnamed: 89.1, 90.2, IC11.12
unnamed: 91.2, IC11.14
unnamed: 91.1, T3.B
unnamed: 92.1, 95.1, T3.C
unnamed: 93.1, 94.1, IC11.5
unnamed: 95.2, 96.1, C39.1, IC11.6
unnamed: 96.2, C39.2, IC11.7, PULSE2.1
unnamed: 98.2, 99.1, 101.1, 109.1, IC11.1, IC11.13, INV_SAW2.1
unnamed: 97.2, 98.1, CENTER2.1, IC11.2
unnamed: 99.2, 100.1, D9.C, IC11.9
unnamed: D9.A, D10.C, IC11.8
unnamed: 100.2, 102.2, D10.A
unnamed: 101.2, 102.1, 103.1, 104.2, IC12.13
unnamed: 109.2, 110.1, IC12.2
unnamed: 110.2, 117.1, IC12.1, SAW2.1
unnamed: 115.2, C34.2, IC15.7, SUB_SQR_5.1
unnamed: 116.2, C33.2, IC15.1, SUB_SQR_6.1
unnamed: 111.2, 112.2, 115.1, C34.1, IC15.6
unnamed: 113.2, 114.2, 116.1, C33.1, IC15.2
unnamed: 117.2, 118.2, 119.2
unnamed: 119.1, IC13.9, ST9.1
unnamed: 120.1, 121.1, 122.2, 123.1, C35.1, IC13.13
unnamed: 123.2, 129.1, C35.2, IC13.14, SUB_SAW_5.1
unnamed: 126.2, IC13.7, ST12.1
unnamed: 128.2, 129.2, 130.1
unnamed: 128.1, IC13.6, ST11.1
unnamed: 124.1, 125.1, 126.1, 127.1, C36.1, IC13.2
unnamed: 124.2, C36.2, IC13.1, SUB_SAW_6.1
unnamed: 131.1, 132.2, IC12.6
unnamed: C38.2, IC14.2, IC14.5
unnamed: 112.1, 122.1, IC14.1, IC14.11
unnamed: C37.2, IC14.9, IC14.12
unnamed: 113.1, 125.2, IC14.13
unnamed: 104.1, 105.2, IC12.14, TRIANGLE2.1
unnamed: 105.1, 108.1, D11.A, D12.C, IC12.10
unnamed: 106.1, 107.2, IC12.9
unnamed: 107.1, IC12.8, SINE2.1
unnamed: 103.2, SYMMETRY2.1
unnamed: 120.2, IC13.8, ST10.1
unnamed: 133.1, 134.2, IC16.12
unnamed: 135.2, IC16.14
unnamed: 135.1, T4.B
unnamed: 136.1, 139.1, T4.C
unnamed: 137.1, 138.1, IC16.5
unnamed: 139.2, 140.1, C55.1, IC16.6
unnamed: 140.2, C55.2, IC16.7, PULSE3.1
unnamed: 142.2, 143.1, 145.1, 153.1, IC16.1, IC16.13, INV_SAW3.1
unnamed: 141.2, 142.1, CENTER3.1, IC16.2
unnamed: 143.2, 144.1, D13.C, IC16.9
unnamed: D13.A, D14.C, IC16.8
unnamed: 144.2, 146.2, D14.A
unnamed: 145.2, 146.1, 147.1, 148.2, IC17.13
unnamed: 153.2, 154.1, IC17.2
unnamed: 154.2, 161.1, IC17.1, SAW3.1
unnamed: 159.2, C50.2, IC20.7, SUB_SQR_7.1
unnamed: 160.2, C49.2, IC20.1, SUB_SQR_8.1
unnamed: 155.2, 156.2, 159.1, C50.1, IC20.6
unnamed: 157.2, 158.2, 160.1, C49.1, IC20.2
unnamed: 161.2, 162.2, 163.2
unnamed: 163.1, IC18.9, ST13.1
unnamed: 164.1, 165.1, 166.2, 167.1, C51.1, IC18.13
unnamed: 167.2, 173.1, C51.2, IC18.14, SUB_SAW_7.1
unnamed: 170.2, IC18.7, ST16.1
unnamed: 172.2, 173.2, 174.1
unnamed: 172.1, IC18.6, ST15.1
unnamed: 168.1, 169.1, 170.1, 171.1, C52.1, IC18.2
unnamed: 168.2, C52.2, IC18.1, SUB_SAW_8.1
unnamed: 175.1, 176.2, IC17.6
unnamed: C54.2, IC19.2, IC19.5
unnamed: 156.1, 166.1, IC19.1, IC19.11
unnamed: C53.2, IC19.9, IC19.12
unnamed: 157.1, 169.2, IC19.13
unnamed: 148.1, 149.2, IC17.14, TRIANGLE3.1
unnamed: 149.1, 152.1, D15.A, D16.C, IC17.10
unnamed: 150.1, 151.2, IC17.9
unnamed: 151.1, IC17.8, SINE3.1
unnamed: 147.2, SYMMETRY3.1
unnamed: 164.2, IC18.8, ST14.1
unnamed: 178.1, 179.2, IC21.2, LEVEL1.1
unnamed: 181.2, 182.1, IC21.13
unnamed: 189.2, 190.1, IC21.9
unnamed: 185.2, C68.2
unnamed: 186.2, C69.2
unnamed: 187.2, C70.2
unnamed: 177.1, C65.1, NOISE_IN.1
unnamed: 180.1, C65.2, IC21.3
unnamed: 179.1, C66.1, IC21.1, LEVEL2.1
unnamed: 183.2, C66.2, IC21.12
unnamed: 182.2, C67.1, IC21.14, WHITE_OUT.1
unnamed: 184.1, 185.1, 186.1, 187.1, 188.1, C71.2, IC21.10
unnamed: 184.2, C67.2
unnamed: 190.2, 191.1, IC21.8, PINK_OUT.1
unnamed: 191.2, 192.1, 193.1, C72.2
unnamed: 193.2, C73.2, IC21.6
unnamed: 192.2, C73.1, IC21.7, RED_OUT.1
PW_CV: 1.2, PW_CV.1
PW_CV1: 9.2, PW_CV1.1
PW_CV2: 89.2, PW_CV2.1
PW_CV3: 133.2, PW_CV3.1
SQR: DCO_TIMER.1, IC5.3
SQR1: DCO_TIMER1.1, IC9.3
SQR2: DCO_TIMER2.1, IC14.3
SQR3: DCO_TIMER3.1, IC19.3

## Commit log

2017-09-25 Initial schematics for waveshaper
2017-09-27 Working with board layout
2017-09-28 Still doing layout
2017-09-28 Routing complete except for bypass caps
2017-09-29 Finished tracing, working on labels
2017-09-30 Trace and text complete, gp and logo missing
2017-10-03 Renamed. Tested 330k resistor and pulse input, updated schematics. Comparison to breadboarded circuit still needed, then only logo and gp is remaining
2017-10-05 Probably final version before adding gp and stuff
2017-10-05 Added ground plane
2017-10-06 Added logo, only panelizing is missing
2018-01-27 New versions
2020-02-12 Testing jlcpcb
2020-02-12 Added part numbers
2020-02-14 Added version 2 of waveshaper, adds a screw hole, moves bypass caps to top and only uses one cap for opamps (per Small/Yusynth). Changes most entry points to ends for resistors/caps
2020-02-17 Vector xonik logo
2020-02-18 Added bom
2020-02-18 Better clearance around bypass caps
2020-02-18 Updated parts list after parts moved
2020-02-20 Split dedication and version
2020-02-20 Silk screen tweak
2020-02-22 Changed to logo-as-component
2020-02-22 Slight silk adjustment
2020-02-23 Added info about trimmer value
2020-03-02 Added bom and gerber
2020-06-16 v2.1 - fixed serious bug, had mixed up + and - on -2.5v generator op amp
2020-06-21 Replaced 1.5k R19 with 1.2k for a sine closer to +/-5v
2023-12-12 will remove resistor divider
2023-12-25 Split connector into 19p + 5p to use available from JLCPB
2023-12-26 Changed pin spacing to 2.54mm to still fit breadboard
2023-12-26 Changed comment about flipflop voltage
2023-12-26 Changed to R0603 and 3v3 operation
2024-02-22 Updated component values after simulation
2024-02-22 Changed size and number of decoupling caps
2024-02-25 Version 2.2 that does not need digital voltage and pulse input
2024-02-27 Reduced footprints for op amps
2024-02-28 Almost all tracing done!
2024-02-28 Finished tracing but not satisfied with placement of GND
2024-02-28 Fixed GND placement
2024-02-28 Better ordering of outputs
2024-02-29 Trying to normalize
2024-02-29 Fixed part names
2024-02-29 Cleaned up and error checked
2024-03-01 Changed waveshaper to -5V
2024-04-16 Changed pins to smaller ones
2024-04-28 Comment about bipolar PWM
2024-05-18 Updated with bipolar pwm
2024-05-26 cleanup
2024-05-28 prepared for single connector
2024-05-29 Switched to single connector
2024-05-31 Updated footprints
2024-06-02 Checked with JLCPCB
2024-06-04 Changed to standard value on waveshaper comparator pullup
2024-06-08 Updated caps and footprint
2024-06-24 Replaced LM311 with SO08 because TSSOP is sold out at JLCPCB
2024-06-25 Increased via outer diameter
2024-11-29 Info about trimming
2024-12-07 Added v2.3 of waveshaper to allow for C0G 100nF caps
2024-12-30 Replaced LM311 with op amp comparator
2024-12-30 Routed new version of comparator
2024-12-31 Improved cap footprint
2025-01-02 Comment about testing
2025-01-21 Fixed polarity issue on square wave output
2025-07-07 v2.4, fixes ground plane noise
2025-07-07 Preparing for doing 4 layer board
2025-08-01 Converted to 4 layer and fixed all issues
2025-08-01 Fixed silk screen
2025-08-10 V2.4 4-layer, bom and gerber tested ok
